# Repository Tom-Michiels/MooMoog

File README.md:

# Compact D — two-board sloped synthesizer

<table>
  <tr>
    <td width="50%"><br><sub><b>Rear</b> — audio jacks and USB ports</sub></td>
    <td width="50%"><br><sub><b>Exploded</b> — panel, control PCB, rails and electronics PCB</sub></td>
  </tr>
  <tr>
    <td width="50%"><br><sub><b>Interior</b> — sloped control board above the flat electronics board</sub></td>
    <td width="50%"><br><sub><b>Control PCB</b> — 19 pots, 8 encoders, 17 switches</sub></td>
  </tr>
</table>

<sub>Renders use reconstructed component models, not certified vendor CAD.</sub>

Active revision: [Split R0.5](hardware/split-r0.5/README.md).

A 220 × 150-mm control PCB under a 15° aluminium panel and a separate 210 × 90-mm electronics PCB, joined by a soldered 12-wire ribbon. CNC wooden sides, PMMA front/rear/bottom, classical printed knobs and the official maakleerplek wordmark. Panel screws now have dedicated clear borders.

- [Control PCB underside](hardware/split-r0.5/previews/control-pcb-underside.png)
- [Electronics PCB](hardware/split-r0.5/previews/electronics-pcb.png)
- [Control KiCad project](hardware/split-r0.5/control/control.kicad_pro)
- [Core KiCad project](hardware/split-r0.5/core/core.kicad_pro)
- [Electrical architecture and cable pinout](hardware/split-r0.5/architecture.md)
- [Enclosure and fabrication detail](mechanical/split-r0.5/README.md)
- [Laser engraving](mechanical/split-r0.5/panel-engraving-paths.svg)
- [Full CAD assembly](mechanical/split-r0.5/split-enclosure-and-boards.step)
- [Remaining verification](hardware/split-r0.5/remaining-verification.md)

Audio input removed. MCP internal contact pull-ups used. No added SMD packages on the carrier boards; purchased modules retain their factory SMD electronics. Current counts: 19 pots, 8 encoders, 17 switches and one power LED.

**Detailed design, not production-ready.** 53 known-pad connection trajectories are routed. Many final physical footprints are still unverified and their missing connections cannot be counted by DRC. Detailed renders use reconstructed component models, not certified vendor CAD. USB keyboard power from the ARCELI board remains unverified. No Gerbers or copper-milling release.

The [completion audit](hardware/split-r0.5/reports/completion-audit.json) compares the functional terminal list against actual KiCad pads: **246 required terminals currently lack matching pads, across 45 padless component instances**. These counts include functional module terminals whose physical mapping must still be established. Run `scripts/audit_completion_r05.py` with KiCad Python; it deliberately returns failure while completion blockers remain. A documented Same Sky SJ1-3523N candidate footprint is now available under `core/libraries/Documented.pretty`; it is **not yet installed on the active board**, because its board-edge and panel fit must be redesigned together.

Older revisions remain historical. The original specification is in `docs/projectspecification-v1.0.md`; decisions and user changes are in `docs/decisions.md`.

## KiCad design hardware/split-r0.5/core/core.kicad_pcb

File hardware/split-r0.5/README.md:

# Compact D R0.5 — two-board sloped design

This revision implements the agreed split: a sloped control PCB and a separate flat electronics PCB, connected by soldered ribbon cable. It removes external audio input, its controls, the ADC, the overload LED, the external contact pull-up bank and optional speaker amplifier. **This is a detailed design revision, not a manufacturing release.** Several purchased-module/pot/switch footprints remain unverified; those components have no fabricated pad patterns.

## Delivered files

- `control/control.kicad_pro`, `.kicad_sch`, `.kicad_pcb`: control-board project, 220 × 150 mm.
- `core/core.kicad_pro`, `.kicad_sch`, `.kicad_pcb`: electronics-board project, 210 × 90 mm.
- `design-master.json`, `controls.csv`, `switches.csv`, `scan.csv`, `ribbon.csv`: common design data and exact functional connections.
- `previews/`: assembled front/rear, exploded assembly, control PCB top/underside, electronics PCB, and native KiCad renders.
- `../../mechanical/split-r0.5/`: full FreeCAD/STEP assembly, detailed reconstructed component models, CNC side STEP files, provisional laser-cut SVGs, aluminium engraving, printed knobs/caps/clamps and Blender scene.
- `architecture.md`: wiring, scanning, pull-ups, audio and USB power decisions.
- `remaining-verification.md`: specific unresolved information, without repeating known dimensions.

## Mechanical design

15° aluminium top panel, 18-mm CNC-cut wood sides, 3-mm dark PMMA front/rear/bottom. The control PCB sits under the aluminium; the electronics PCB sits horizontally on bottom spacers. Internal rails support the control PCB independently of the visible panel screws. Printed bridges clamp the ribbon at both boards so cable movement does not pull directly on solder joints.

The new screw border increases the aluminium panel to **246 × 172 mm**. Both PCBs remain within the user's 220 × 150-mm maximum. Enclosure outside dimensions are approximately **266 × 172.1 × 104.5 mm including knobs and feet**. Front wood height is 47.2 mm; rear wood height 93.3 mm. These are design proposals, not measured stock-material dimensions.

The six panel screws sit outside the lettering. A raster check of the vector artwork confirms a **4.5-mm clear radius around every screw centre**. Actual head radius in the model is 2.7 mm, leaving 1.8 mm additional clearance to engraving. The official maakleerplek SVG wordmark is taken from https://maakleerplek.be/nl and incorporated unchanged in shape, with a monochrome colour for engraving. The original SVG is preserved with source information.

## What “realistic” means here

The new renders use explicit geometry for module PCBs, headers, individual IC leads, shields, antenna traces, USB mouths/tongues, audio jacks, resistors, capacitors, control housings, shafts, screws and cable. Copper in the Blender views is exported from the actual KiCad segment data, not invented decorative tracks. Native KiCad views use the same locally generated WRL models.

These are **detailed reconstructed models**, not exact vendor STEP files. Unpublished header offsets, shaft/bushing heights and connector details remain assumptions. A photorealistic render cannot prove those fit. See `remaining-verification.md` and the earlier per-product source audit at `sources/amazon-dimensions-r04.md`.

## Electrical and routing status

74 functional components, 19 pots, 8 encoders, 17 switches, 41 digital contacts, one power LED. All **added carrier-board resistors/capacitors are through-hole**; factory-built Amazon modules naturally still contain their own SMD components. There are 12 resistors, 4 ceramic capacitors and 2 electrolytics; two I²C pull-up resistors are DNP unless measurements show they are needed.

53 connection trajectories between currently available pads have been routed: 33 on the control board and 20 on the core board. DRC has no remaining violations or unconnected items **among those pads**. This does **not** mean the boards are electrically complete: 45 component instances still lack final pads, so DRC cannot see their missing connections. Firmware, full USB power verification, audio gain/coupling, return-path/ground-plane design, final routing, production footprints and hardware tests remain outstanding. There is no Gerber or CNC-copper release.

The functional schematic netlists match the design data; ribbon pin assignments match at both ends. Models pass CAD validity checks. Nominal inter-board envelopes retain at least 11.7 mm conservative vertical separation where their projections overlap. This is not a substitute for physical fit checks on the actual modules.

## Reproduction

Run `build_split_r05.py` with KiCad Python, then `route_split_r05.py export/route/apply` for each board (export/apply require KiCad Python; route uses normal Python). Apply once to freshly generated boards. Export pads/tracks with `export_split_pads_r05.py`, generate the panel with `build_panel_r05.py`, generate CAD with `build_split_cad_r05.py` using FreeCAD Python, then render with `render_split_r05.py` in Blender. Cutting diagrams and print-cap variants have separate R05 scripts. `check_split_r05.py` checks exported netlists, DRC reports and nominal inter-board geometry. Do not regenerate over manual edits without saving them first.

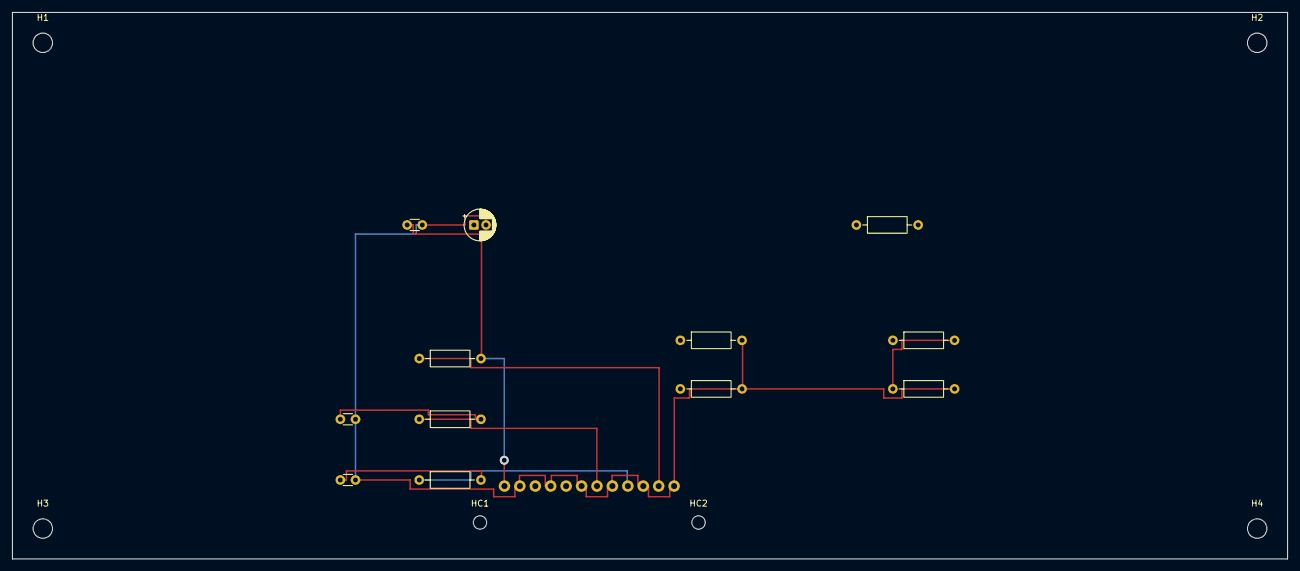
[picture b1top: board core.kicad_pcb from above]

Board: 2 copper layers, 210.0 x 90.0 mm, 23 parts (0 on the bottom side), 8 nets.

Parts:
CA1, CA2: 1nF; C_Disc_D3.0mm_W1.6mm_P2.50mm
CC1: 100nF; C_Disc_D3.0mm_W1.6mm_P2.50mm
CC2: 10uF 10V; CP_Radial_D5.0mm_P2.00mm
DAC1: PCM5102 / L main, R phones
H1, H2, H3, H4: MountingHole_3.2mm_M3
HC1, HC2: MountingHole_2.2mm_M2
HP1: Quystetes TPA6132 module
JCORE: 12-way soldered ribbon
JMAIN: 3.5mm MAIN output / MPN pending
MCU1: ARCELI ESP32-S3 N16R8
RA1, RA2: 1k; R_Axial_DIN0207_L6.3mm_D2.5mm_P10.16mm_Horizontal
RA3: 100R; R_Axial_DIN0207_L6.3mm_D2.5mm_P10.16mm_Horizontal
RA4: 10k; R_Axial_DIN0207_L6.3mm_D2.5mm_P10.16mm_Horizontal
RA5: 4k7; R_Axial_DIN0207_L6.3mm_D2.5mm_P10.16mm_Horizontal
RA6, RA7: 100k; R_Axial_DIN0207_L6.3mm_D2.5mm_P10.16mm_Horizontal
RP5: 10k; R_Axial_DIN0207_L6.3mm_D2.5mm_P10.16mm_Horizontal

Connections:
3V3: CC1.1, JCORE.1, RP5.2
GND: CA1.2, CA2.2, CC1.2, CC2.2, JCORE.2, JCORE.4, JCORE.6, JCORE.8, JCORE.10, JCORE.12, RA5.2, RA6.2, RA7.2
HP_FEED: RA4.2, RA5.1
PANEL_IRQ: JCORE.11, RP5.1
POT_ADC1: JCORE.7, RA1.1
POT_ADC1_FILTER: CA1.1, RA1.2
POT_ADC2: JCORE.9, RA2.1
POT_ADC2_FILTER: CA2.1, RA2.2

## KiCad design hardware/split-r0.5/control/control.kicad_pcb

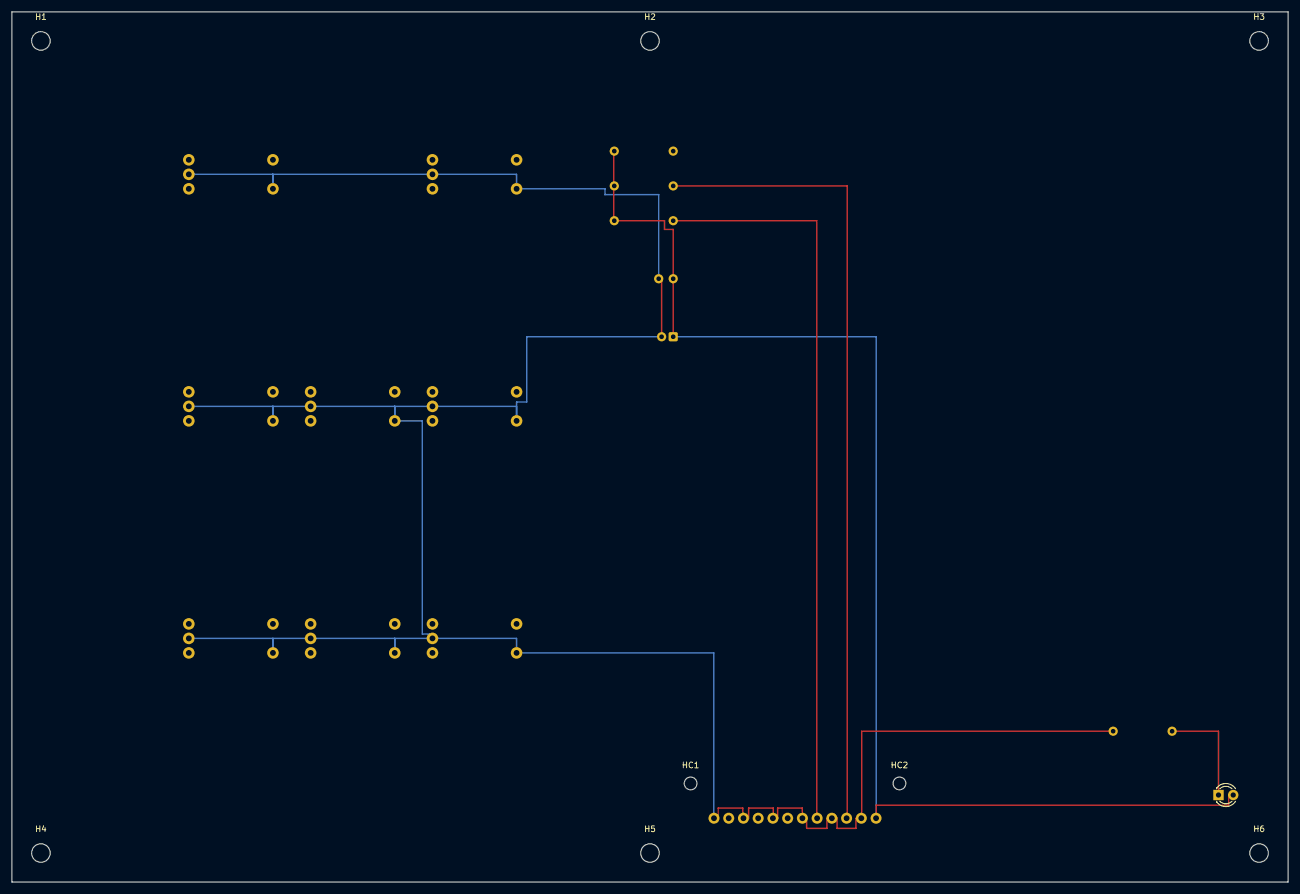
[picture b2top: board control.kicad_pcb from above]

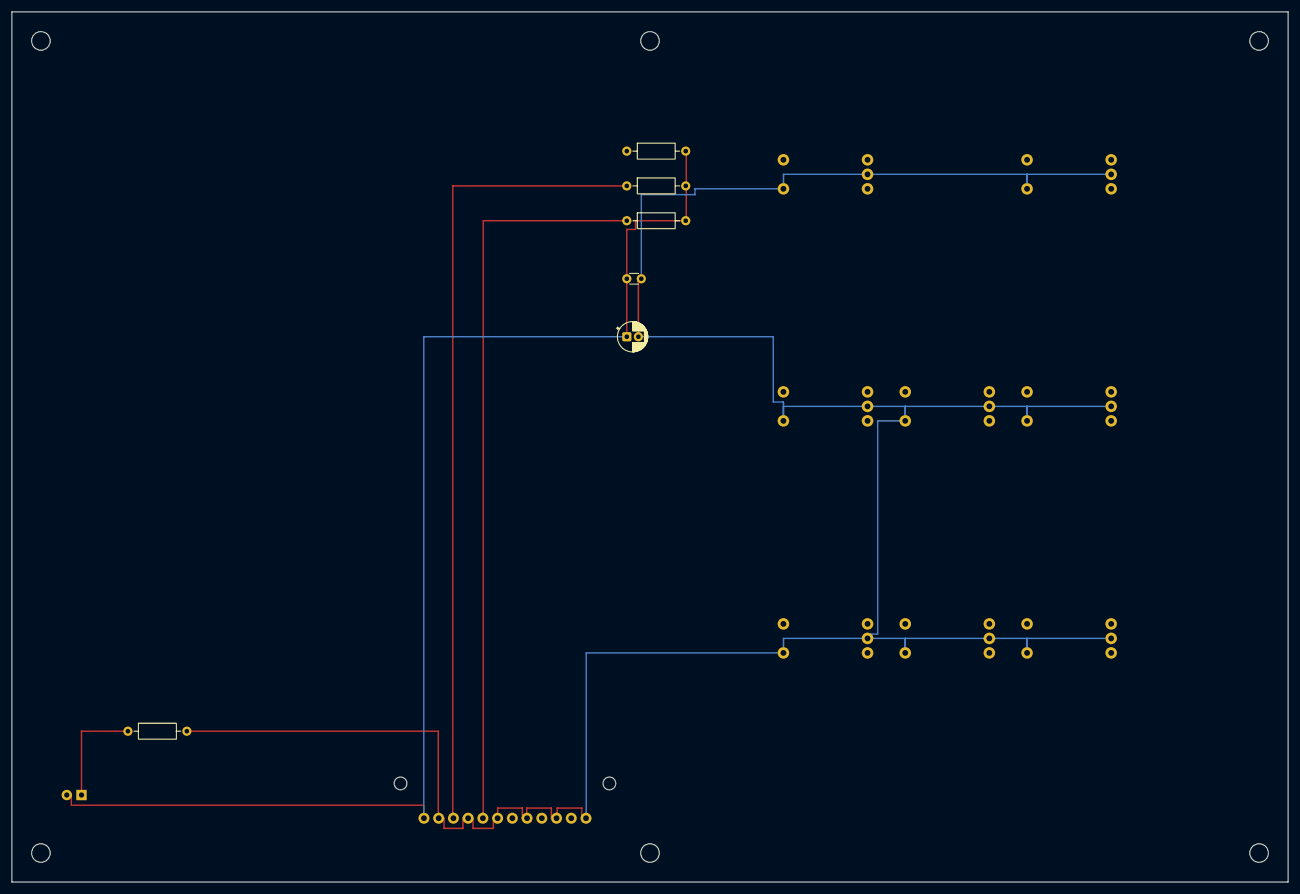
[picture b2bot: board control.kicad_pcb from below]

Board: 2 copper layers, 220.0 x 150.0 mm, 65 parts (12 on the bottom side), 5 nets.

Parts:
CP1: 100nF; C_Disc_D3.0mm_W1.6mm_P2.50mm
CP2: 10uF 10V; CP_Radial_D5.0mm_P2.00mm
E1: EC11 RANGE; E1
E2: EC11 WAVEFORM; E2
E3: EC11 RANGE; E3
E4: EC11 FREQUENCY; E4
E5: EC11 WAVEFORM; E5
E6: EC11 RANGE; E6
E7: EC11 FREQUENCY; E7
E8: EC11 WAVEFORM; E8
H1, H2, H3, H4, H5, H6: MountingHole_3.2mm_M3
HC1, HC2: MountingHole_2.2mm_M2
IO1: MCP23017 module / 0x20
IO2: MCP23017 module / 0x21
IO3: MCP23017 module / 0x22
JPANEL: 12-way soldered ribbon
LED2: Power LED; LED_D3.0mm
MX1, MX2: CD74HC4067 module
RP1: 1k; R_Axial_DIN0207_L6.3mm_D2.5mm_P10.16mm_Horizontal
RP2: 10k; R_Axial_DIN0207_L6.3mm_D2.5mm_P10.16mm_Horizontal
RP3, RP4: 2k2 DNP; R_Axial_DIN0207_L6.3mm_D2.5mm_P10.16mm_Horizontal
RV1: RK097N B10K TUNE
RV2: RK097N B10K GLIDE
RV3: RK097N B10K MODULATION MIX
RV4: RK097N B10K LFO RATE
RV5, RV6, RV7, RV19: RK097N B10K VOLUME
RV9: RK097N B10K NOISE VOLUME
RV10: RK097N B10K CUTOFF FREQUENCY
RV11: RK097N B10K EMPHASIS
RV12: RK097N B10K AMOUNT OF CONTOUR
RV13, RV16: RK097N B10K ATTACK TIME
RV14, RV17: RK097N B10K DECAY TIME
RV15, RV18: RK097N B10K SUSTAIN LEVEL
RV20: RK097N B10K PHONES
S1: Osc mod
S2: Osc3 / EG
S3: Noise / LFO
S4: Glide on
S5: Decay on
S6: LFO shape
S7: Osc3 keyboard
S8: Osc 1 on
S9: Osc 2 on
S10: Osc 3 on
S12: Noise on
S13: White / Pink
S14: Filter mod
S15: Keytrack 1
S16: Keytrack 2
S17: Main on
S18: A-440

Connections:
3V3: CP1.1, CP2.1, JPANEL.1, LED2.2, RP2.2, RP3.2, RP4.2
GND: CP1.2, CP2.2, E1.C, E1.SW2, E2.C, E2.SW2, E3.C, E3.SW2, E4.C, E4.SW2, E5.C, E5.SW2, E6.C, E6.SW2, E7.C, E7.SW2, E8.C, E8.SW2, JPANEL.2, JPANEL.4, JPANEL.6, JPANEL.8, JPANEL.10, JPANEL.12, RP1.2
I2C_SCL: JPANEL.5, RP4.1
I2C_SDA: JPANEL.3, RP3.1
PWR_LED: LED2.1, RP1.1
